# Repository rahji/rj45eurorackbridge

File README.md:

# Portable RJ45-to-Eurorack Bridge

## A system that allows impromptu collaboration between Eurorack modular synthesists, while maintaining an appropriate distance during the COVID-19 pandemic.

This is essentially a breakout for a shielded RJ45 jack. Each of the 8 pins of the RJ45 jack is connected to the tip of a 3.5mm jack (the Eurorack standard for patch cables). Connecting a *shielded* Ethernet cable between two of these essentially allows eight CV or audio signals to reach across a long distance, from one modular synth to another.

### Ideas

* You and your collaborator each build one of these, then meet up and create sound together, while maintaining a safe distance.
* Or make two (Oshpark gives you 3 boards anyway!) and keep them with your modular travel case for impromptu collaborations.
* Consider working/performing outdoors, over a fence, from neighboring houses, or in separate cars.
* Indoors, try collaborating blindly while in separate rooms without telling each other what kind of signal is on each of the jacks. Change them mid-performance.
* Labeling the jacks isn't so useful if your partner labels them differently. That fine though - that might force experimentation, chance, and fortunate mishaps.
* Come up with some kind of system of rules that provides structure for chance happenings: the left four jacks are for inputs, the right are for outputs; or one person sends gates or envelopes through the left jacks and the other person returns audio on the opposite jacks. (Accidentally connecting an output to an output generally isn't a problem in Eurorack - nothing should blow up.)
* Think about collaboration in terms of live performance or as two different recordings to be made simulataneously by each of the collaborators.
* Come up with a more unidirectional scenario: maybe one person supplies a different looping sample on each of the eight jacks and the other must use them in their composition. Then switch roles at some point.
* Use a cable that will provide you the CDC-recommended social distance. Maybe see what happens with an extremely long cable combined with a very loud PA at both ends. Or a Twitch live stream from both ends. Or a phone call?

### Build

1. Make the circuitboard using the files provided or [import it directly to OSH Park](https://oshpark.com/import?url=https://raw.githubusercontent.com/rahji/rj45eurorackbridge/master/eagle/RJ45_EURORACK_BRIDGE_castellated.brd)
2. Solder the required components
  * 1 x Wurth Elecktronik Shielded Ethernet Connector p/n 615008140421 from [Mouser](https://www.mouser.com/ProductDetail/Wurth-Elektronik/615008140421?qs=%2Fha2pyFadujj32eJSvwd90ECqRKXOEYbwVGH%2FNq2N1eMDIxBQFOhvg%3D%3D)
  * 8 x PJ301M-12 3.5mm switching mono jacks (aka Thonkiconn) from [Thonk](https://www.thonk.co.uk/shop/3-5mm-jacks/), [AI Synthesis](https://aisynthesis.com/product/3-5mm-eurorack-jack-thonk-pj301m-12/), [Control](https://www.ctrl-mod.com/products/3-5mm-eurorack-jacks), [synthCube](https://synthcube.com/cart/3-5mm-euro-jacks), etc
3. Make an enclosure using the template provided or purchase a Hammond Manufacturing 1590A diecast aluminum enclosure p/n 1590A from [Mouser](https://www.mouser.com/ProductDetail/Hammond-Manufacturing/1590A?qs=lxPAlgZqN%2Fx6Rw4O%2FIXFww%3D%3D)
4. Get a hold of a *shielded* ethernet cable  

### Build Tips

* Remember that Oshpark gives you 3 PCBs when you order!
* If you use a different PCB fab service, make sure the castellated holes aren't going to be a problem (ie: they should to be plated)
* When soldering the jacks on, it's easiest if you bend in the pin that connects to the castellated hole before inserting it into the pcb. Heat the pin from the outside and apply solder at the point where the castellated hole is.
* Consider soldering the 3.5mm jacks on first, then the ethernet jack. Otherwise, it won't sit flat on the table when you try to solder the 3.mm jacks.
* You'll need to make a rectangular hole in the enclosure for the ethernet jack. If you're using a diecast aluminum enclosure, it's easiest to do this with a milling machine but you can also drill a hole and carefully turn it into a rectangle using a triangular file.

### FAQ

- **Haven't I seen this before?**
  - Other patch cable bridges/busses definitely exist, although I've only seen them as modules or integrated into a case. The idea with this one is that it's portable, shareable, and doesn't take up real estate in the case when you're not collaborating. With that said, you can of course use it to connect two of your own cases, as you would with a module like Intellijel's Octalink, the Doepfer A-180-9, or the ADDAC213 Eurorack Bridge.

- **Can I connect this to an ethernet hub/switch or a computer?**
  - Don't do that. Don't connect the other end of the ethernet cable to anything other than another one of these devices. You could probably connect it to one of the modules listed in the previous FAQ but I haven't tried it.

- **Can I make these and sell them?**
  - The [GPL license](https://github.com/rahji/rj45eurorackbridge/blob/master/LICENSE) allows you to do this, with certain conditions. This is meant to be an inexpensive DIY project, not an overpriced product for you to sell at a 300% markup on Tindie. No matter what, please don't remove the Black Lives Matter silkscreen (see below).

- **Why does the PCB say Black Lives Matter?**
  - Because it's an important message to have anywhere and everywhere. See https://github.com/rahji/blacklivesmatter-eagle-lib

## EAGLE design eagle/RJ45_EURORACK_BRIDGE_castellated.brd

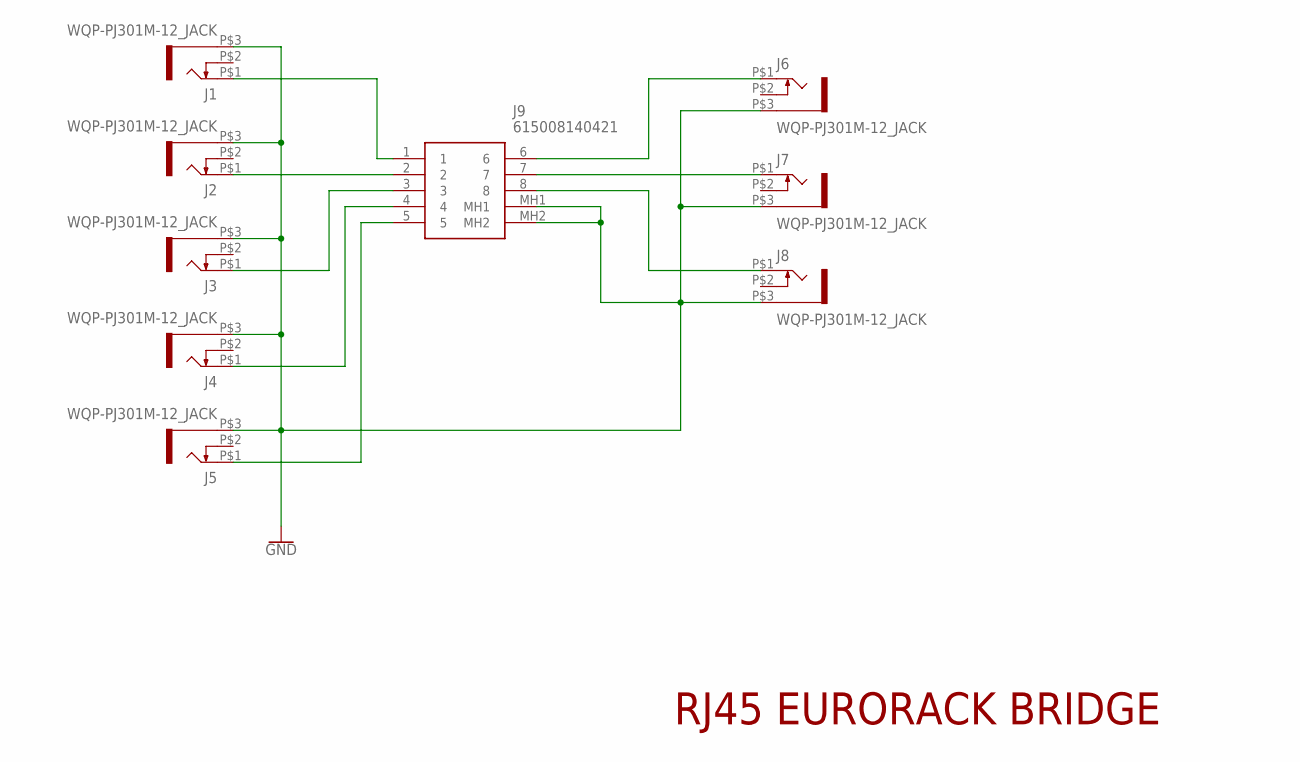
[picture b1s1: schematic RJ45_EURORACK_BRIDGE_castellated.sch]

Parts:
J1, J2, J3, J4, J5, J6, J7, J8: WQP-PJ301M-12_JACK
J9: 615008140421

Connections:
GND: J1.P$3 (1), J2.P$3 (1), J3.P$3 (1), J4.P$3 (1), J5.P$3 (1), J6.P$3 (1), J7.P$3 (1), J8.P$3 (1), J9.MH1, J9.MH2
unnamed: J2.P$1 (2), J9.2
unnamed: J6.P$1 (2), J9.6
unnamed: J7.P$1 (2), J9.7
unnamed: J8.P$1 (2), J9.8
unnamed: J1.P$1 (2), J9.1
unnamed: J3.P$1 (2), J9.3
unnamed: J4.P$1 (2), J9.4
unnamed: J5.P$1 (2), J9.5

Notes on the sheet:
RJ45 EURORACK BRIDGE

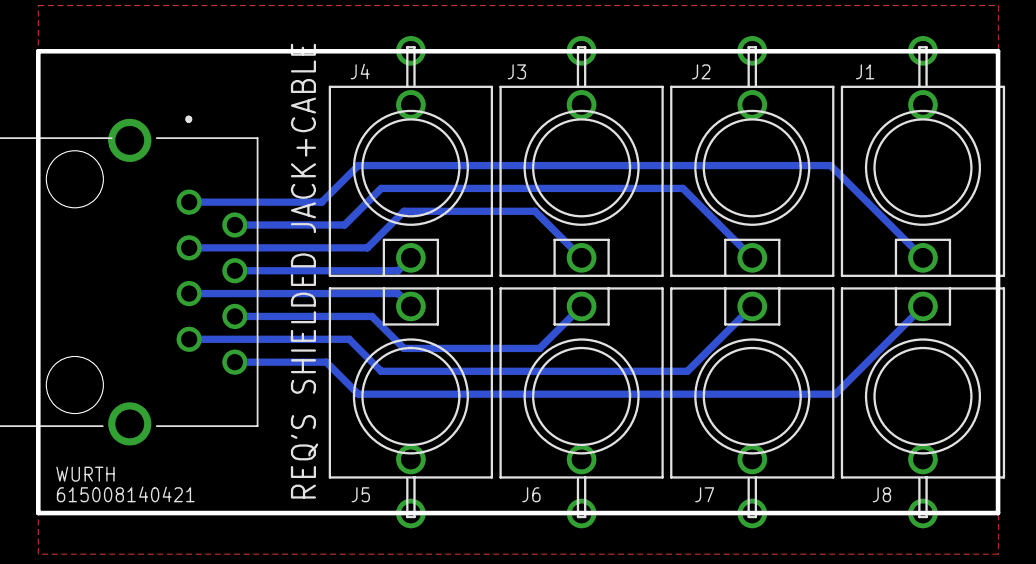
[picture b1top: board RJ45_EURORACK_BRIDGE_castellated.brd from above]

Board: 2 copper layers, 53.3 x 25.7 mm, 9 parts (0 on the bottom side), 9 nets.

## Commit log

2020-07-06 Initial Add of Files
2020-07-06 Updated README with photos
2020-07-07 Added photo of PCB back and front
2021-01-25 Updated OSH Park link to use their API

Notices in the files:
parts and their libraries:
SparkFun-PowerSymbols: Licensing: Creative Commons ShareAlike 4.0 International - https://creativecommons.org/licenses/by-sa/4.0
